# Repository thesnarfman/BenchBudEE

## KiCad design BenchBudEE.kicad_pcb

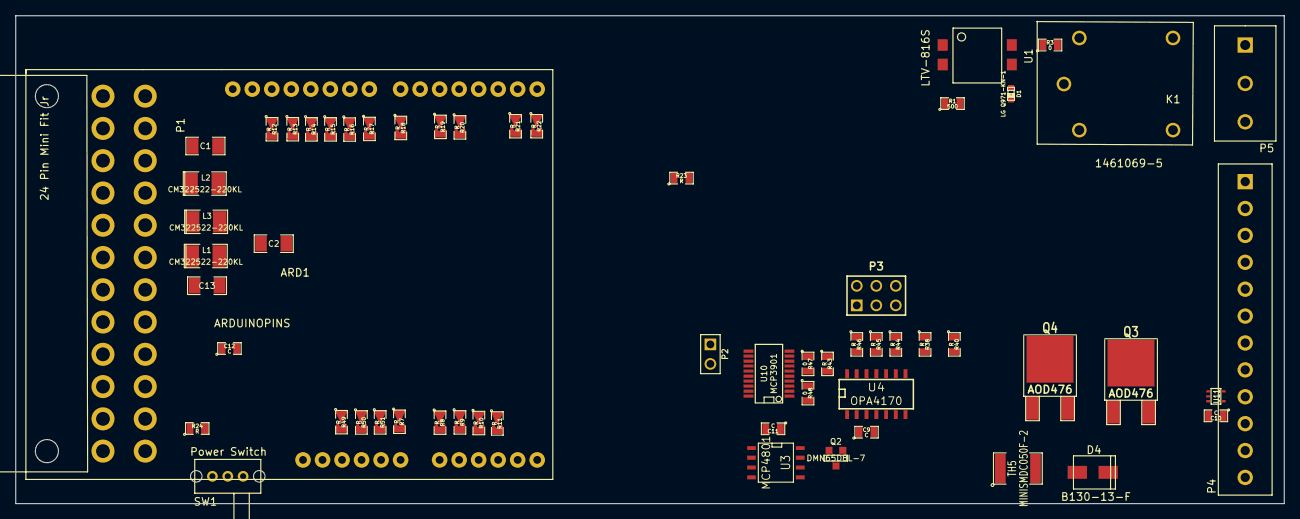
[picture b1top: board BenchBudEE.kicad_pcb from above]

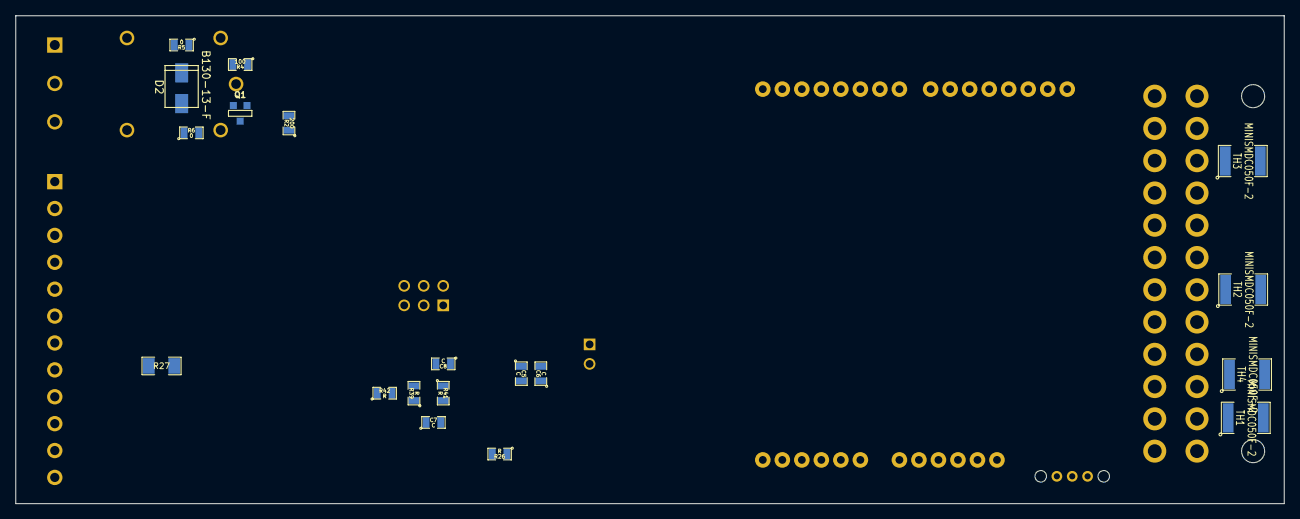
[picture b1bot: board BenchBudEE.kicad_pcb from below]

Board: 4 copper layers, 165.1 x 63.5 mm, 79 parts (19 on the bottom side), 79 nets, no tracks yet.

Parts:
ARD1: ARDUINOPINS; Arduino
C1, C2, C13: C; SM1206
C5, C6, C7, C8, C9, C10, C11, C12: C; SM0805
D1: LG Q971-KN-1; LED-0603
D2, D4: B130-13-F; SMA
K1: 1461069-5; TE-SPDT
L1, L2, L3: CM322522-220KL; SM1210L
P1: 24 Pin Mini Fit Jr; ATX_Header
P2: CONN_2; PIN_ARRAY_2X1
P3: CONN_3X2; pin_array_3x2
P4: 12 Pin Terminal Block; 12pinTB
P5: 3 Pin TB; 3pinTB
Q1: MMBT3904-7-F; SOT23EBC
Q2: DMN65D8L-7; SOT23GDS
Q3, Q4: AOD476; DPAK2
R1: 500; SM0805
R2: 200; SM0805
R3, R5, R6, R47, R48: 0; SM0805
R4: 100; SM0805
R7, R8, R9, R10, R11, R12, R13, R14, R15, R16, R17, R18, R19, R20, R21, R22, R49, R50, R51: R; SM0805-Blob
R23, R24, R26, R38, R39, R40, R41, R42, R43, R44, R45, R46: R; SM0805
R27: R; SM1206
SW1: Power Switch; BB_switch
TH1, TH2, TH3, TH4, TH5: MINISMDC050F-2; SM1812
U1: LTV-816S; 4-SMD
U3: MCP4801; SO8N
U4: OPA4170; SO14E
U10: MCP3901; SSOP20
U11: LMT84; SOT353

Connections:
+3.3V: P4.1, R24.2, TH1.2
+5V: C5.2, C6.1, C10.1, C11.2, C13.1, L1.2, P4.2, R49.1, TH2.2, U3.1, U10.2, U10.3, U11.4
+12C: C12.1, P1.10, TH3.1, TH5.1
+12P: L2.1, R3.2, R5.2, R7.1, TH3.2
+12V: C1.1, C9.2, L2.2, U4.4
-12P: L3.1, TH4.2
-12V: C2.2, C8.2, L3.2, U4.11
/Arduino/CURR_MEAS: Q3.2, Q4.3, R10.1, R27.1, U4.2
/Arduino/FAN_MODE: Q3.1, R22.2
/Arduino/FAN_PWM: Q2.G, R15.2
/Arduino/MISO: R13.2, U10.19
/Arduino/MOSI: R14.2, U3.4, U10.20
/Arduino/RELAY+: R21.2, U1.1
/Arduino/RELAY-: R1.2, R23.2
/Arduino/SCLK: R12.2, U3.3, U10.18
/Arduino/~ADC_CS: R17.2, U10.17
/Arduino/~DR: R20.2, U10.14
/Arduino/~RESET: R19.2, U10.1
/Fan/CS_N: R18.2, U3.2
/Fan/FAN_OUT+: D4.2, P4.8, TH5.2
/Fan/FAN_OUT-: D4.1, P4.9, Q4.2
/Fan/TACH_IN: P4.10, R11.1
/Relay/RELAY_COM: K1.1, P5.2
/Relay/RELAY_NC: K1.4, P5.3
/Relay/RELAY_NO: K1.3, P5.1
/Thermo_Couple/CH0+: C7.1, U4.7, U10.4
/Thermo_Couple/CH0-: C7.2, R48.2, U10.5
/Thermo_Couple/CH1+: U10.7, U11.3
/Thermo_Couple/CH1-: R47.2, U10.6
/Thermo_Couple/TC_IN +: P4.11, U4.10
/Thermo_Couple/TC_IN -: P4.12, U4.12
AGND: C5.1, C6.2, C8.1, C9.1, C10.2, C11.1, C12.2, Q2.S, Q3.3, R27.2, R39.1, R47.1, R48.1, U3.7, U10.8, U10.11, U11.1, U11.2
GND: C1.2, C2.1, C13.2, P1.3, P1.5, P4.3, R2.1, R6.1, R23.1, R50.1, R51.1, SW1.3
unnamed: ARD1.12, R21.1
unnamed: ARD1.16, R19.1
unnamed: ARD1.4, R7.2
unnamed: ARD1.1, R49.2
unnamed: ARD1.2, R50.2
unnamed: ARD1.3, R51.2
unnamed: ARD1.21, R15.1
unnamed: ARD1.15, R20.1
unnamed: ARD1.8, R11.2
unnamed: ARD1.7, R10.2
unnamed: ARD1.6, R9.2
unnamed: ARD1.20, R16.1
unnamed: ARD1.19, R17.1
unnamed: ARD1.11, R22.1
unnamed: ARD1.5, R8.2
unnamed: ARD1.18, R18.1
unnamed: ARD1.22, R14.1
unnamed: ARD1.23, R13.1
unnamed: ARD1.24, R12.1
unnamed: R43.1, R44.2, R45.2, R46.2, U4.13
unnamed: P3.6, R44.1
unnamed: P3.4, R45.1
unnamed: P3.2, R46.1
unnamed: P2.1, U10.12
unnamed: P2.2, U10.13
unnamed: R38.2, R40.1, U4.6
unnamed: P3.1, P3.3, P3.5, R42.2, U4.9
unnamed: R40.2, R42.1, U4.8
unnamed: R39.2, R41.1, U4.5
unnamed: R41.2, R43.2, U4.14
unnamed: D2.1, K1.5, Q1.3
unnamed: R1.1, U1.2
unnamed: R3.1, U1.4
unnamed: D1.2, R2.2
unnamed: D2.2, K1.2, R5.1
unnamed: Q1.1, R6.2
unnamed: Q1.2, R4.2
unnamed: D1.1, R4.1, U1.3
unnamed: R24.1, SW1.1
unnamed: P1.16, SW1.2
unnamed: P1.14, TH4.1
unnamed: P1.4, P1.6, TH2.1
unnamed: P1.2, TH1.1
unnamed: R26.1, U3.8
unnamed: Q2.D, R26.2, U4.3
unnamed: Q4.1, U4.1

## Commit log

2014-02-02 Initial File Creation
2014-02-02 Add hierarchical labels
2014-02-04 Wire Up general Thermocouple
2014-02-05 Create Initial Fan Module Schematic
2014-02-05 Initial Relay Module Schematic Wire Up
2014-02-05 Wire up Power Schematic
2014-02-05 Added Power Control Monitoring Module Schematic
2014-02-05 Create Arduino Schematic and Wire Up top Level
2014-02-09 Upgrade Current/Fan Output Schem Use PWM
2014-02-17 Initial Relay PCB Layout
2014-02-20 Added Arduino Connect Pin Layout
2014-02-23 Associate and Place Power Component
